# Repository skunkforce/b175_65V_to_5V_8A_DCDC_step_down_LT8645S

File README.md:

# edgy_board number b175
This design is part of the [edgy board project](https://github.com/skunkforce/edgy_boards). It provides an 8 Amp step-down from up to 65V using LT8645S. 

# getting started
This repository uses submodules. After cloning, use the command 

```$ git submodule update --init --recursive```

To pull the submodules before opening the project with Kicad. 

# Tests
Tests can be found in [TESTS.md](TESTS.md)

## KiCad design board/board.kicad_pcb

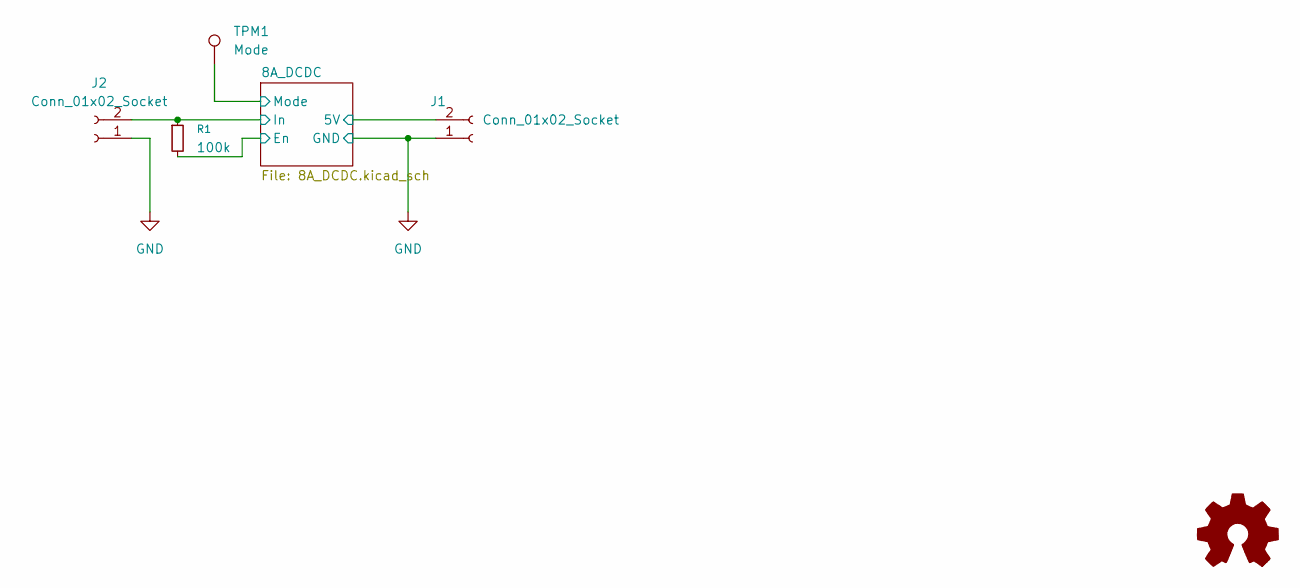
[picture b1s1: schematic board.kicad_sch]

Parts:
J1, J2: Conn_01x02_Socket; TerminalBlock_MaiXu_MX126-5.0-02P_1x02_P5.00mm
LOGO1: Logo_Open_Hardware_Small; OSHW-Symbol_6.7x6mm_SilkScreen
R1: 100k; R_0603_1608Metric; lcsc C25803
TPM1: Mode; TestPoint_Pad_2.0x2.0mm

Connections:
/8A_DCDC/5V: J1.2; also elsewhere on the board
/8A_DCDC/En: R1.2; also elsewhere on the board
/8A_DCDC/In: J2.2, R1.1; also elsewhere on the board
/8A_DCDC/Mode: TPM1.1; also elsewhere on the board
GND: J1.1, J2.1; also elsewhere on the board

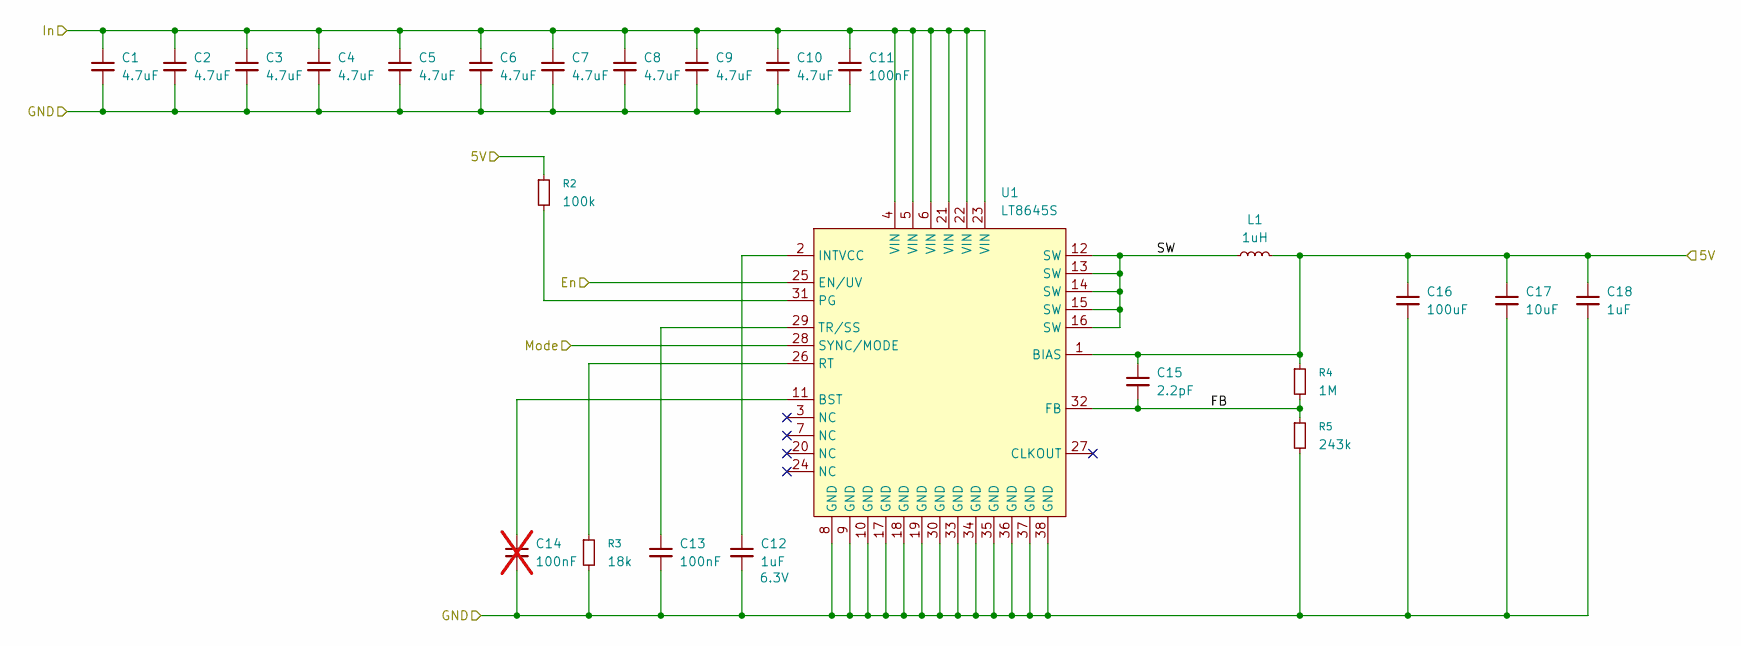
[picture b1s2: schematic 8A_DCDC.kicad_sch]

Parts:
C1, C2, C3, C4, C5, C6, C7, C8, C9, C10: 4.7uF; C_1210_3225Metric; lcsc C385986
C11: 100nF; C_0805_2012Metric; lcsc C28233
C12: 1uF; C_0603_1608Metric; Voltage 6.3V; lcsc C15849
C13: 100nF; C_0603_1608Metric; lcsc C14663
C14: 100nF; C_0603_1608Metric; not fitted
C15: 2.2pF; C_0603_1608Metric; lcsc C282246
C16: 100uF; C_1206_3216Metric; lcsc C15008
C17: 10uF; C_1206_3216Metric; lcsc C13585
C18: 1uF; C_1206_3216Metric; lcsc C1848
L1: 1uH; L_Coilcraft_XAL6030-XXX; lcsc C5157561
R2: 100k; R_0603_1608Metric; lcsc C25803
R3: 18k; R_0603_1608Metric; lcsc C25810
R4: 1M; R_0603_1608Metric; lcsc C22935
R5: 243k; R_0603_1608Metric; lcsc C22917
U1: LT8645S; LQFN-32-6EP_4x6mm_P0.5mm; Digikey 505-LT8645SEV#PBF-ND

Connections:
/8A_DCDC/5V: C15.1, C16.1, C17.1, C18.1, L1.2, R2.1, R4.1, U1.1 (BIAS); also elsewhere on the board
/8A_DCDC/En: U1.25 (EN/UV); also elsewhere on the board
/8A_DCDC/FB: C15.2, R4.2, R5.1, U1.32 (FB)
/8A_DCDC/In: C1.1, C2.1, C3.1, C4.1, C5.1, C6.1, C7.1, C8.1, C9.1, C10.1, C11.1, U1.4 (VIN), U1.5 (VIN), U1.6 (VIN), U1.21 (VIN), U1.22 (VIN), U1.23 (VIN); also elsewhere on the board
/8A_DCDC/Mode: U1.28 (SYNC/MODE); also elsewhere on the board
/8A_DCDC/SW: L1.1, U1.12 (SW), U1.13 (SW), U1.14 (SW), U1.15 (SW), U1.16 (SW)
GND: C1.2, C2.2, C3.2, C4.2, C5.2, C6.2, C7.2, C8.2, C9.2, C10.2, C11.2, C12.2, C13.2, C14.2, C16.2, C17.2, C18.2, R3.2, R5.2, U1.8 (GND), U1.9 (GND), U1.10 (GND), U1.17 (GND), U1.18 (GND), U1.19 (GND), U1.30 (GND), U1.33 (GND), U1.34 (GND), U1.35 (GND), U1.36 (GND), U1.37 (GND), U1.38 (GND); also elsewhere on the board
unnamed: C14.1, U1.11 (BST)
unnamed: C12.1, U1.2 (INTVCC)
unnamed: R2.2, U1.31 (PG)
unnamed: R3.1, U1.26 (RT)
unnamed: C13.1, U1.29 (TR/SS)

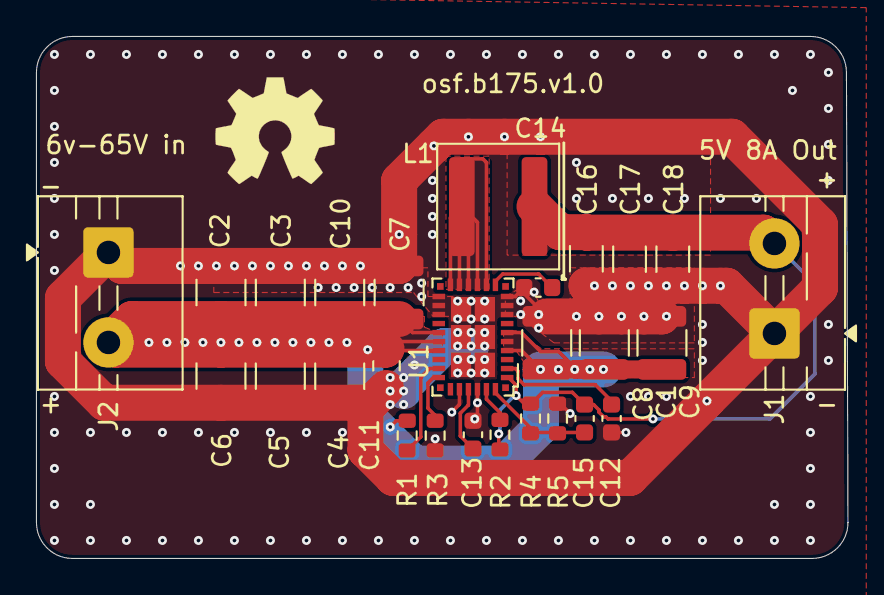
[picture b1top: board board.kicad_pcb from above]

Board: 2 copper layers, 45.1 x 29.0 mm, 29 parts (1 on the bottom side), 12 nets.

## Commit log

2025-10-03 initial
